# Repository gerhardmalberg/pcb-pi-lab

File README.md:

# PCB Power Integrity Lab

- **DC power delivery network (PDN):** supply and return voltage drops, differential load
  voltages, current distribution, effective resistance and copper loss.
- **AC power delivery network:** driving-point and transfer impedance,
  resonances, decoupling comparisons and target-impedance checks.
- **Load transients:** supply droop, overshoot and settling under finite-rise-time
  load steps and pulses, with comparisons between capacitor populations.
- **Steady electrothermal coupling:** copper heating, PCB temperature and
  temperature-dependent resistance, followed by AC and transient analysis at the
  converged temperature.

These are standalone CPU workflows.
Original software, documentation and synthetic fixtures are Apache-2.0.

KiCad supplies saved geometry; Gmsh meshes it; Elmer solves conduction and heat;
ngspice solves the attached circuit. Python checks conservation and produces
reports. ParaView opens the same voltage, current-density and temperature fields.
No hardware checkout or sibling lab source tree is required.

**Model boundary:** resistance is extracted from PCB geometry. Inductance,
effective capacitance, ESR, ESL and mounting parasitics are explicit circuit
inputs. This release does not extract broadband AC fields, model skin effect,
verify regulator control-loop stability, or predict device junction temperatures.
It has no CUDA execution path.

## How it works

The diagram follows `--analysis all`. A `dc` run stops after the cold electrical
solution; individual AC and transient runs first resolve the electrothermal
prerequisite. The board is read without modification or copper refilling.

```mermaid
flowchart TD
    board["Saved KiCad board<br/>Copper, pads, nets, layers and plated holes"]
    case["Versioned JSON case<br/>Terminals, materials, cooling, circuit models and limits"]
    extract["Extract and validate geometry<br/>Keep electrical nets and layers separate"]
    mesh["Gmsh: shared conformal mesh<br/>Selected copper for current; board materials for heat"]
    basis["Elmer: independent terminal excitations<br/>Resolve supply and return resistance"]
    network["Terminal conductance network"]
    dc["ngspice: DC source and load circuit<br/>Solve terminal voltages and currents"]
    fields["Reconstruct physical potential field<br/>Calculate current density and spatial Joule heating"]
    heat["Elmer: steady heat conduction<br/>Apply cooling and explicitly assigned component heat"]
    converge{"Temperature and electrical<br/>convergence passed twice?"}
    update["Under-relax temperature<br/>Update copper conductivity"]
    frozen["Converged resistance network<br/>Hold temperature fixed"]
    models["Explicit circuit parasitics<br/>Source impedance, inductance, capacitance, ESR and ESL"]
    ac["ngspice: AC current injection<br/>Driving-point and transfer impedance"]
    transient["ngspice: finite-edge load steps and pulses<br/>Droop, overshoot and settling"]
    checks["Check conservation, numerical accuracy and design limits<br/>Compare capacitor populations and refine transient timestep"]
    outputs["Reports, CSVs, plots, checks and provenance<br/>Native Elmer results, editable SPICE decks and ParaView fields"]

    board --> extract
    case --> extract
    extract --> mesh --> basis --> network --> dc --> fields --> heat --> converge
    fields -.->|Cold DC baseline| outputs
    converge -->|No: continue within iteration limit| update --> basis
    converge -->|Yes| frozen
    models --> dc
    models --> ac
    models --> transient
    frozen --> ac
    frozen --> transient
    ac --> checks
    transient --> checks
    checks --> outputs
```

Invalid inputs, failed solvers, failed conservation checks or electrothermal
nonconvergence stop the run. Solver completion, numerical validity and design-limit
compliance are reported separately. Mesh refinement is a separate verification
workflow; `verify` checks input, implementation and result hashes.

## Quick start

To view the example in KiCad 10, open
[board.kicad_pro](examples/synthetic-pdn/board.kicad_pro) in the project manager,
then double-click `board.kicad_pcb`. This is a PCB-only simulation fixture;
the source, loads and capacitor models are defined in `case.json` and the
generated SPICE decks. No schematic or external footprint libraries are required
to inspect the saved board.
The board is centered on landscape A4; its grid and auxiliary origins are at the
upper-left board corner. The [presentation update](docs/validation.md#board-presentation-update)
records its geometry equivalence to the original validation input and explains
the effect of cosmetic edits on file-hash verification.

Use Linux x86-64, Python 3.11+ and rootless Podman. The host requires no numerical
Python packages. The checkout launcher runs pinned numerical tools in a container.

```bash
./pcb-pi build
./pcb-pi doctor
./pcb-pi test --integration
./pcb-pi run examples/synthetic-pdn/case.json --analysis all
./pcb-pi verify examples/synthetic-pdn/case.json
```

`build` reuses the existing tools image identified in `env/runtime.json` and adds
the pinned ngspice package. Its upstream image is not required to have a local
source checkout. On a fresh machine, build independently:

```bash
./pcb-pi build --from-scratch
```

This downloads hash-verified assets and builds the lab's own base/tools recipes.
It can take hours and substantially more disk than the reused-image build. Keep
at least 20 GiB free. No image export or duplicate large download is needed for
the normal installed-image path. Tool sources and pins are under `env/`.

For an optional shell command from any directory, install this checkout editable:

```bash
python3 -m venv .venv
. .venv/bin/activate
python -m pip install -e .
pcb-pi doctor
```

Keep the checkout in place. Set `PCB_PI_ENGINE` to select a compatible container
engine, or `PCB_PI_IMAGE` to select an explicitly built image. The image's actual
identity enters every run's provenance and cache key.

## Analyses

```bash
./pcb-pi run examples/synthetic-pdn/case.json --analysis dc
./pcb-pi run examples/synthetic-pdn/case.json --analysis electrothermal
./pcb-pi run examples/synthetic-pdn/case.json --analysis ac
./pcb-pi run examples/synthetic-pdn/case.json --analysis transient
```

`all` computes a cold DC baseline, converges electrical/thermal feedback, then
runs both circuit analyses at the converged temperature. `ac` and `transient`
also resolve the electrothermal prerequisite; they do not silently use cold
resistance. Transients hold that thermal bias fixed. The final thermal solution
and the temperature used to calculate conductivity may differ by the recorded
convergence residual (less than the configured tolerance).

The default electrothermal iteration uses 0.5 relaxation, a 50-iteration limit,
temperature residual below 0.1 C, and electrical metric changes below 0.1% for
two consecutive iterations. Failed convergence or conservation stops the run.

The synthetic fixture has two copper layers, one source, two loads, a narrow
supply track, through vias, a return fill and two optional decoupling capacitors. Its materials,
cooling and parasitics are illustrative assumptions, not qualified hardware data.
See [case configuration](docs/cases.md) and [validation](docs/validation.md).

## Results and inspection

Results default to ignored `results/examples/synthetic-pdn/`:

- `report.md`, `checks.json`: separate solver completion, numerical validation
  and design-limit compliance. A failed design limit does not invalidate a solve.
- `dc/`, `electrothermal/`: conductance matrices, native Elmer inputs/meshes,
  full-precision fields, circuit decks, losses and thermal iteration history.
- `ac/`, `transient/`: editable ngspice decks, logs, impedance/voltage CSVs,
  population comparisons and transient timestep checks.
- `fields/`: VTU fields, `view.pvsm` and `open-view.py` for ParaView.
- `provenance.json`, `checkpoint.json`, stage manifests: source, implementation,
  image identity, completion and artifact hashes. Completed iterations can resume
  only when their input temperature and all other inputs match.

Open VTU files in ParaView, or load `view.pvsm` and relocate its `/output/fields`
data paths to your result directory. Running `open-view.py` with `pvpython`
recreates the state beside the fields. Circuit `.cir` files can be inspected
directly or loaded as SPICE netlists in Qucs-S; no editable Qucs schematic is
generated. All quantities are in SI units except explicitly suffixed mm/C values.

Mesh convergence is deliberately separate from hash verification:

```bash
python3 scripts/verify-convergence.py --scales 1 .25 .1875
```

This sequentially solves the synthetic case at three or more mesh sizes and checks
voltage drop, copper loss and temperature rise, then includes AC and transient
analysis on the accepted mesh. `results/refinement/summary.json` identifies that
mesh's output directory and report. The quick-start run is the coarse member of
this study. Do not infer numerical convergence
or hardware correlation merely from a completed solver run.
The explicit scales reproduce this fixture's release check. Omit `--scales` to
use the longer adaptive sequence when assessing a different case.

## Source preservation and licensing

Inputs are mounted read-only, and extraction never saves or refills a board.
Runs stop when available disk falls below the required reserve at launch.
`--force` replaces only the selected case's generated stage directories.
Nothing is published, pushed or committed by the CLI.

Third-party tools and input designs retain their own licenses. The reused code
and recipe attribution is in [NOTICE](NOTICE). This repository does not change
any upstream hardware design, report or provenance.

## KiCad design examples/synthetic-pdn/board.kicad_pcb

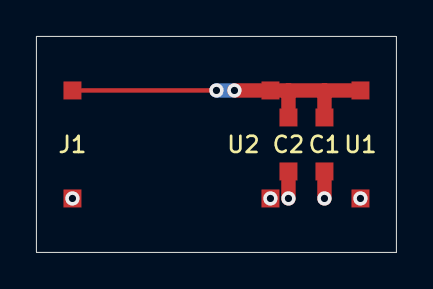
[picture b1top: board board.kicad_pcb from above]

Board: 2 copper layers, 20.0 x 12.0 mm, 5 parts (0 on the bottom side), 2 nets.

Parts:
C1: 10u
C2: 1u
J1: Source
U1: Load 1
U2: Load 2

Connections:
RETURN: C1.2, C2.2, J1.2, U1.2, U2.2
SUPPLY: C1.1, C2.1, J1.1, U1.1, U2.1
